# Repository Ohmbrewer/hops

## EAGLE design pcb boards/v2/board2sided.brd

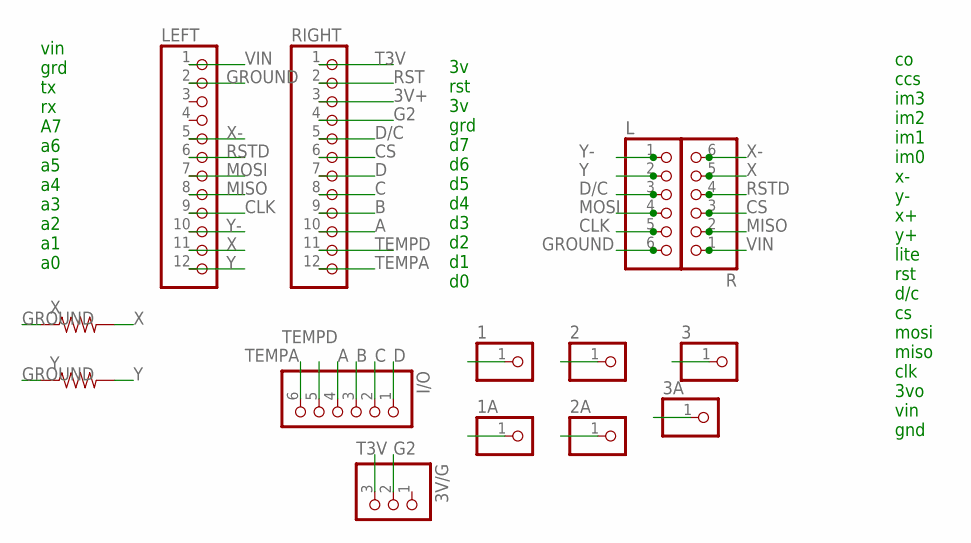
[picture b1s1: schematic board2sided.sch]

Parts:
1, 1A, 2, 2A, 3, 3A: PINHD-1X1CB; 1X01-CLEANBIG
3V/G: PINHD-1X3CB; 1X03-CLEANBIG
I/O: PINHD-1X6CB; 1X06-CLEANBIG
L: PINHD-1X6CB; 1X06-CLEANBIG
LEFT: PINHD-1X12-CB; 1X12-CB
R: PINHD-1X6CB; 1X06-CLEANBIG
RIGHT: PINHD-1X12-CB; 1X12-CB
X: 10KOHM-1/6W-5%(PTH)KIT; AXIAL-0.3-KIT
Y: 10KOHM-1/6W-5%(PTH)KIT; AXIAL-0.3-KIT

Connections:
1: 1.1, 1A.1
2: 2.1, 2A.1
3: 3.1, 3A.1
3V+: RIGHT.3
A: I/O.4, RIGHT.10
B: I/O.3, RIGHT.9
C: I/O.2, RIGHT.8
CLK: L.5, LEFT.9
CS: R.3, RIGHT.6
D: I/O.1, RIGHT.7
D/C: L.3, RIGHT.5
G2: 3V/G.2, RIGHT.4
GROUND: L.6, LEFT.2, X.P$1 (1), Y.P$1 (1)
MISO: LEFT.8, R.2
MOSI: L.4, LEFT.7
RST: RIGHT.2
RSTD: LEFT.6, R.4
T3V: 3V/G.3, RIGHT.1
TEMPA: I/O.6, RIGHT.12
TEMPD: I/O.5, RIGHT.11
VIN: LEFT.1, R.1
X: LEFT.11, R.5, X.P$2 (2)
X-: LEFT.5, R.6
Y: L.2, LEFT.12, Y.P$2 (2)
Y-: L.1, LEFT.10

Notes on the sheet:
vin grd tx rx A7 a6 a5 a4 a3 a2 a1 a0
3v rst 3v grd d7 d6 d5 d4 d3 d2 d1 d0
co ccs im3 im2 im1 im0 x- y- x+ y+ lite rst d/c cs mosi miso clk 3vo vin gnd

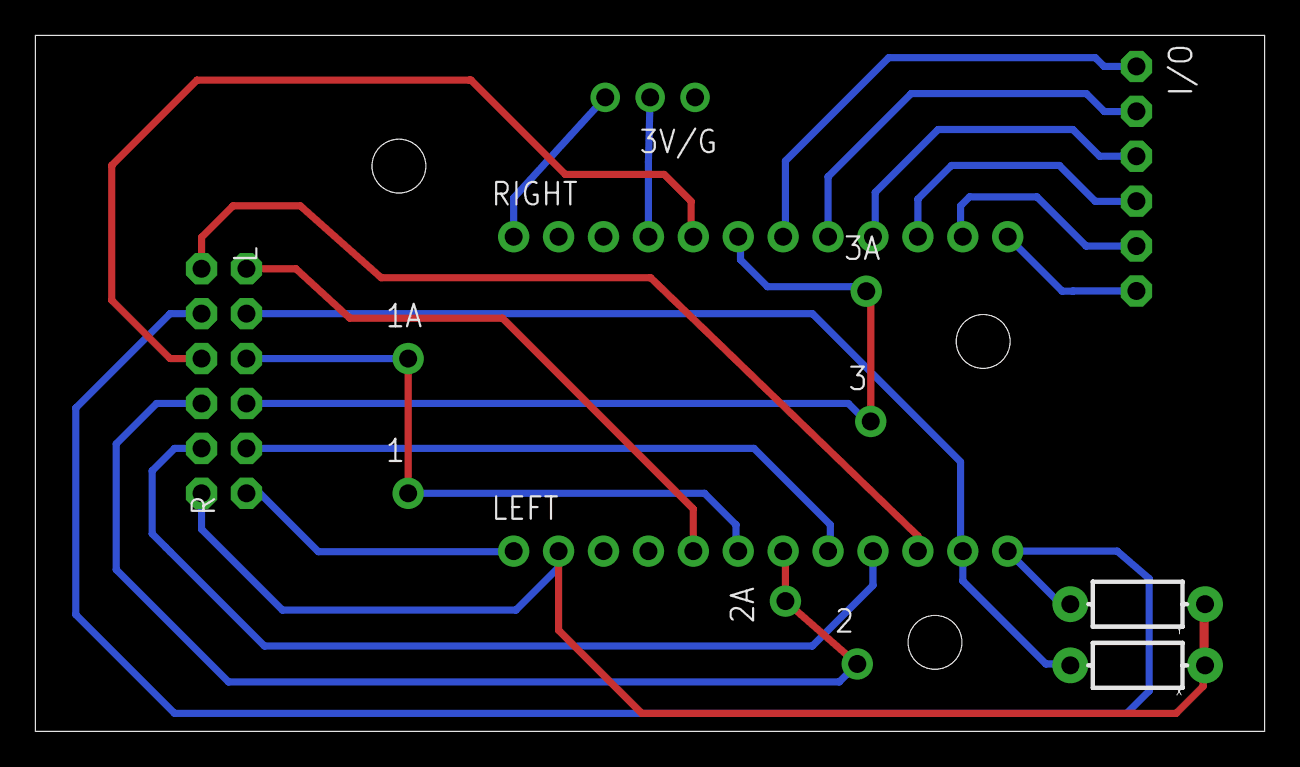
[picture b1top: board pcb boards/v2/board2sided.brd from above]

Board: 2 copper layers, 69.5 x 39.4 mm, 17 parts (0 on the bottom side), 23 nets.

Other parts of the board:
U$1, U$2, U$3: STAND-OFF-TIGHT

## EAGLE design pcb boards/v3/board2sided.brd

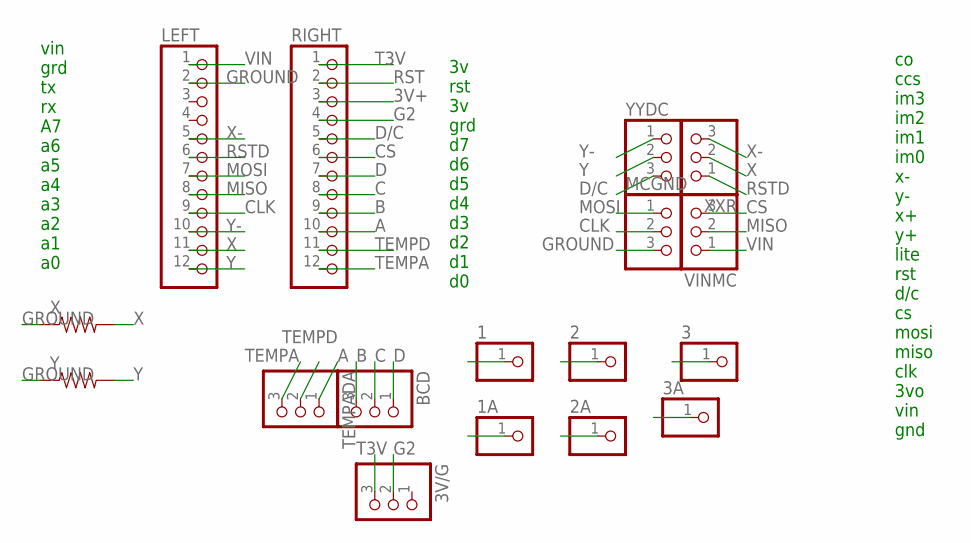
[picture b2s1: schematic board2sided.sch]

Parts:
1, 1A, 2, 2A, 3, 3A: PINHD-1X1CB; 1X01-CLEANBIG
3V/G: PINHD-1X3CB; 1X03-CLEANBIG
BCD: PINHD-1X3CB; 1X03-CLEANBIG
LEFT: PINHD-1X12-CB; 1X12-CB
MCGND: PINHD-1X3CB; 1X03-CLEANBIG
RIGHT: PINHD-1X12-CB; 1X12-CB
TEMPADA: PINHD-1X3CB; 1X03-CLEANBIG
VINMC: PINHD-1X3CB; 1X03-CLEANBIG
X: 10KOHM-1/6W-5%(PTH)KIT; AXIAL-0.3-KIT
XXR: PINHD-1X3CB; 1X03-CLEANBIG
Y: 10KOHM-1/6W-5%(PTH)KIT; AXIAL-0.3-KIT
YYDC: PINHD-1X3CB; 1X03-CLEANBIG

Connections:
1: 1.1, 1A.1
2: 2.1, 2A.1
3: 3.1, 3A.1
3V+: RIGHT.3
A: RIGHT.10, TEMPADA.1
B: BCD.3, RIGHT.9
C: BCD.2, RIGHT.8
CLK: LEFT.9, MCGND.2
CS: RIGHT.6, VINMC.3
D: BCD.1, RIGHT.7
D/C: RIGHT.5, YYDC.3
G2: 3V/G.2, RIGHT.4
GROUND: LEFT.2, MCGND.3, X.P$1 (1), Y.P$1 (1)
MISO: LEFT.8, VINMC.2
MOSI: LEFT.7, MCGND.1
RST: RIGHT.2
RSTD: LEFT.6, XXR.1
T3V: 3V/G.3, RIGHT.1
TEMPA: RIGHT.12, TEMPADA.3
TEMPD: RIGHT.11, TEMPADA.2
VIN: LEFT.1, VINMC.1
X: LEFT.11, X.P$2 (2), XXR.2
X-: LEFT.5, XXR.3
Y: LEFT.12, Y.P$2 (2), YYDC.2
Y-: LEFT.10, YYDC.1

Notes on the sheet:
vin grd tx rx A7 a6 a5 a4 a3 a2 a1 a0
3v rst 3v grd d7 d6 d5 d4 d3 d2 d1 d0
co ccs im3 im2 im1 im0 x- y- x+ y+ lite rst d/c cs mosi miso clk 3vo vin gnd

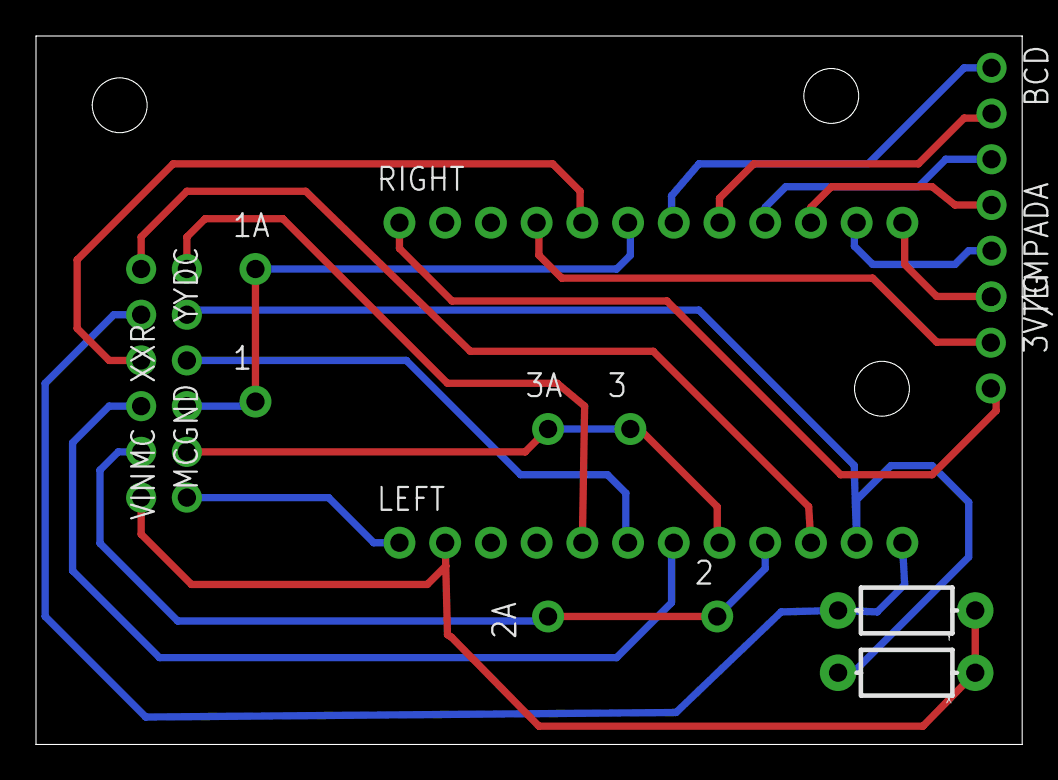
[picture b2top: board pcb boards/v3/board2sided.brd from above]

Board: 2 copper layers, 54.8 x 39.4 mm, 20 parts (0 on the bottom side), 23 nets.

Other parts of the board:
U$1, U$2, U$3: STAND-OFF-TIGHT

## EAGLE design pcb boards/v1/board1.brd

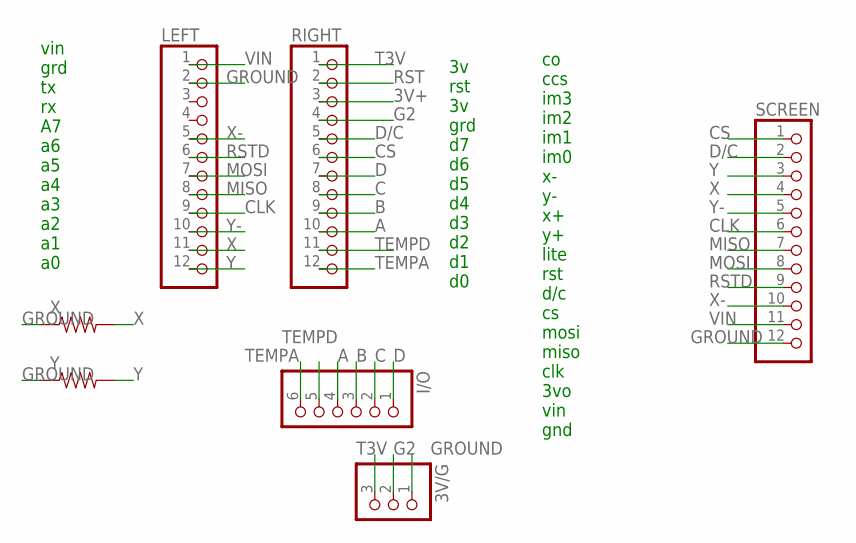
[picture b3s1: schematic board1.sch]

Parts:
3V/G: PINHD-1X3CB; 1X03-CLEANBIG
I/O: PINHD-1X6CB; 1X06-CLEANBIG
LEFT: PINHD-1X12-CB; 1X12-CB
RIGHT: PINHD-1X12-CB; 1X12-CB
SCREEN: PINHD-1X12-CB; 1X12-CB
X: 10KOHM-1/6W-5%(PTH)KIT; AXIAL-0.3-KIT
Y: 10KOHM-1/6W-5%(PTH)KIT; AXIAL-0.3-KIT

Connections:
3V+: RIGHT.3
A: I/O.4, RIGHT.10
B: I/O.3, RIGHT.9
C: I/O.2, RIGHT.8
CLK: LEFT.9, SCREEN.6
CS: RIGHT.6, SCREEN.1
D: I/O.1, RIGHT.7
D/C: RIGHT.5, SCREEN.2
G2: 3V/G.2, RIGHT.4
GROUND: 3V/G.1, LEFT.2, SCREEN.12, X.P$1 (1), Y.P$1 (1)
MISO: LEFT.8, SCREEN.7
MOSI: LEFT.7, SCREEN.8
RST: RIGHT.2
RSTD: LEFT.6, SCREEN.9
T3V: 3V/G.3, RIGHT.1
TEMPA: I/O.6, RIGHT.12
TEMPD: I/O.5, RIGHT.11
VIN: LEFT.1, SCREEN.11
X: LEFT.11, SCREEN.4, X.P$2 (2)
X-: LEFT.5, SCREEN.10
Y: LEFT.12, SCREEN.3, Y.P$2 (2)
Y-: LEFT.10, SCREEN.5

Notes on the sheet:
vin grd tx rx A7 a6 a5 a4 a3 a2 a1 a0
3v rst 3v grd d7 d6 d5 d4 d3 d2 d1 d0
co ccs im3 im2 im1 im0 x- y- x+ y+ lite rst d/c cs mosi miso clk 3vo vin gnd

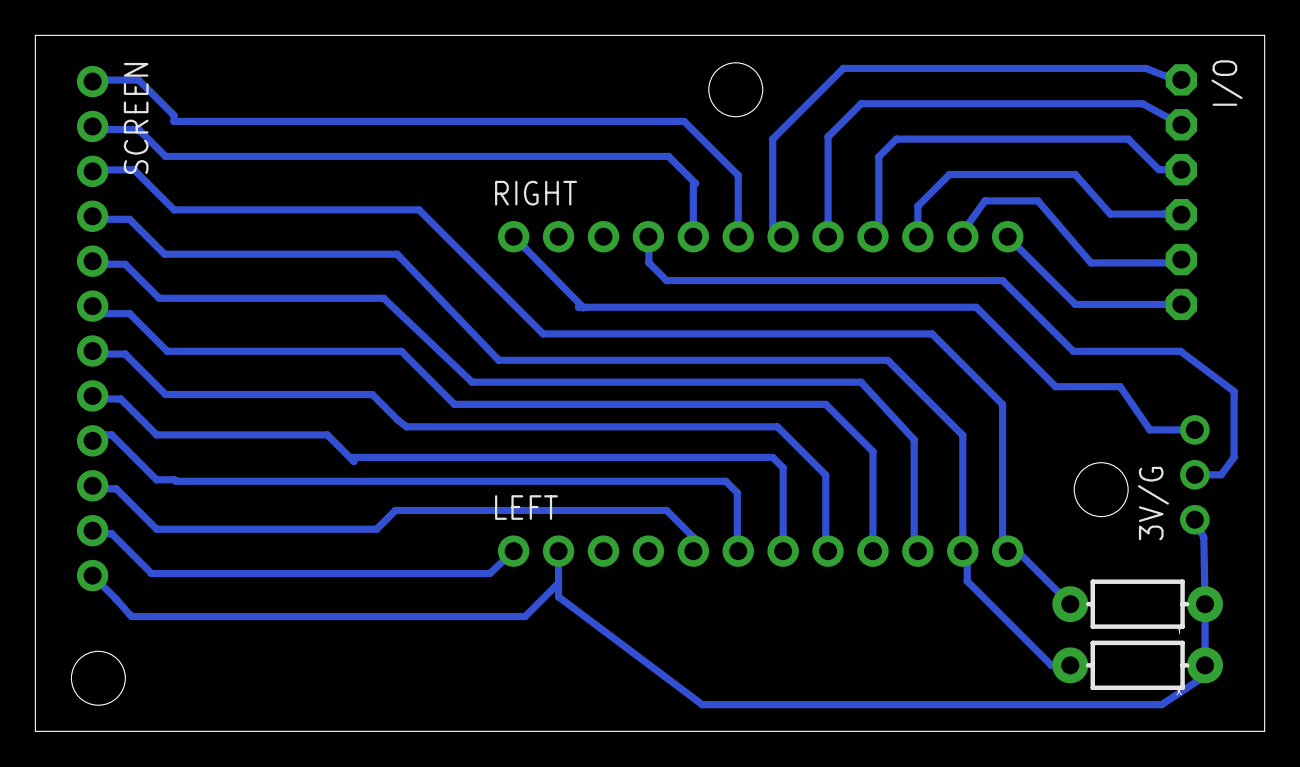
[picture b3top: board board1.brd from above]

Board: 2 copper layers, 69.5 x 39.4 mm, 10 parts (0 on the bottom side), 20 nets.

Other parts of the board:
U$1, U$2, U$3: STAND-OFF-TIGHT

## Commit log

2015-04-03 Initial commit.
2015-04-05 Adds a little example of how to connect to the Spark with Ruby, including updating and viewing a variable.
2015-04-06 Changed the lib reference to require_relative
2015-07-13 creats rhizome.ino
    base compiled rhizome operational instructions, functinoality is not full at the moment, most likely due to something blocking.
2015-07-16 adds pcb board files
2015-07-16 refigures driver code
2015-07-25 Adds a pump program for testing Rhizome messaging.
    This fake pump program demonstrates how to take in settings from a Spark.function and report changes via Spark.publish. Expects a RGB LED wired to A0, A1, and A4.
2015-07-26 Improves the operation of the FakePump rig. Add the beginning of a Cucumber test against that rig that we should be able to subsequently use against a real Rhizome.
2015-07-29 Gets the Operate Pump Cucumber test working. Beware that (in Heroku, at least) it seems like there may be some messaging difficulties (lag, unupdated stuff). Also adds a wiring diagram for the Fake P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
2015-08-01 Uses built-in LED instead of external.
    Removes references to external LED and just uses the RGB function. Adds initial work for stop time support, but commented out.
2015-08-01 New and improved Fake Pump! - Uses the built-in LED so you don't need to wire anything. - Adds a Stop Time at which the pump should stop pumping. - Adds some time expression parsing so our Feature fi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
2015-08-03 Adds an extra comparison when deciding whether to create a Pump webhook. Now it should check whether the given event is associated with the endpoint so we could conceivably have 2+ webhooks for the e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
2015-08-10 Gets the screen driver mostly working
    - Properly displays temperature and relay information in an organized
    way
    - Current Temp color goes from Blue to Yellow to Red as it approaches,
    matches, and passes Target Temp
    - Relay status is Yellow when On and Red when Off
    - Buttons almost work. There’s some calibration to do and but this
2015-08-11 Adds in integration with the FakePump. Also cleans up some of the text color settings.
2015-08-12 Adds an automated test for UC.RE5 - a really basic example test of checking on a temperature sensor. Works with the fake temperature sensor mock.

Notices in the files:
parts and their libraries:
SparkFun-Resistors: Licensing: Creative Commons ShareAlike 4.0 International - https://creativecommons.org/licenses/by-sa/4.0
